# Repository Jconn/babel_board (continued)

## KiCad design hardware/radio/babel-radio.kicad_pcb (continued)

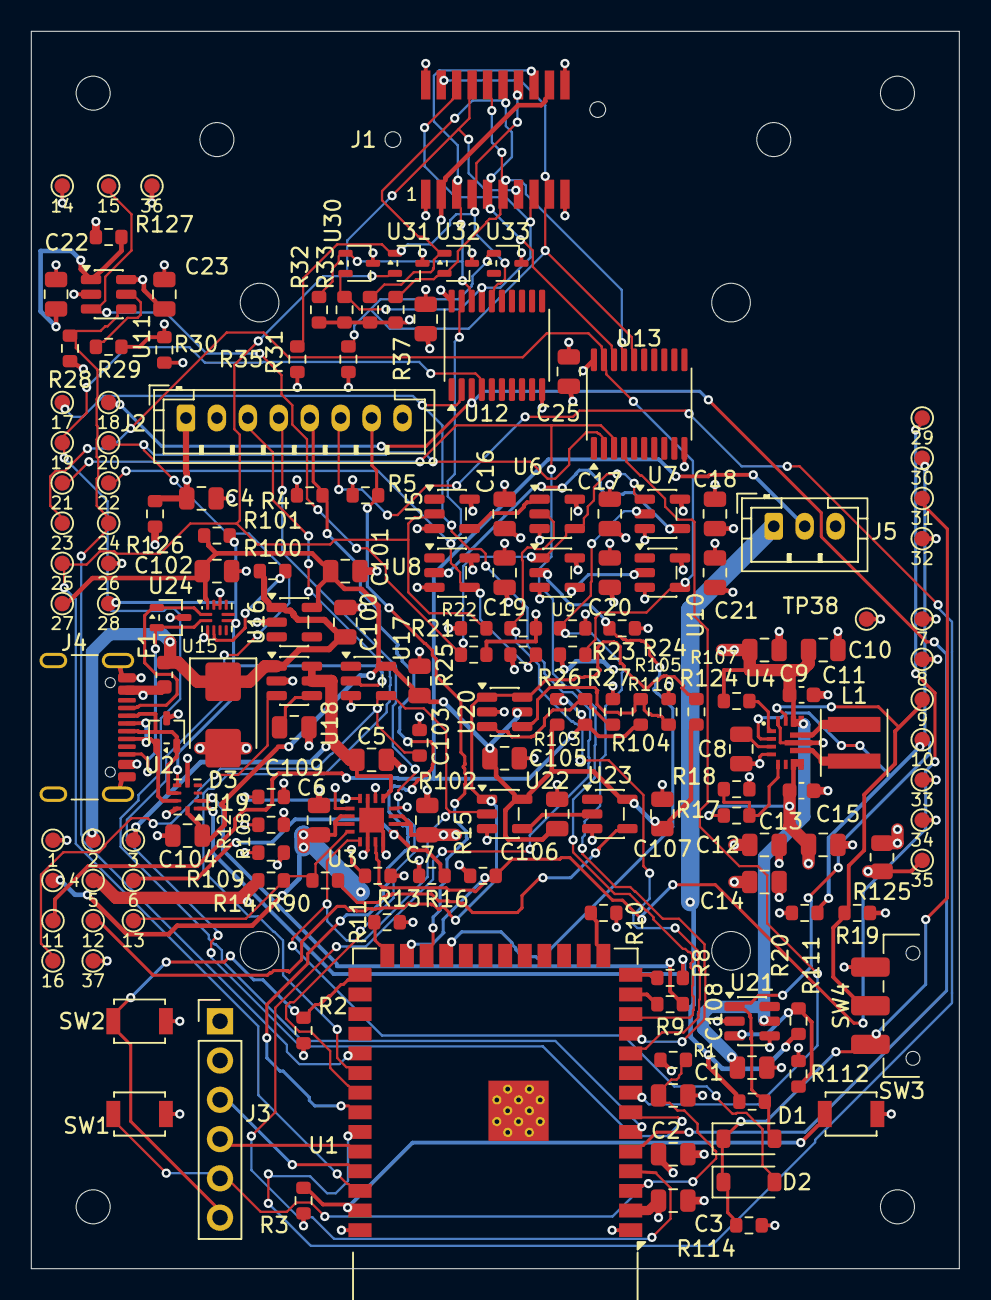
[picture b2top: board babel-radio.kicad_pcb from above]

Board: 4 copper layers, 60.0 x 80.0 mm, 178 parts (0 on the bottom side), 83 nets.

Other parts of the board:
H1, H2, H3, H4, H5, H6, H7, H8, H9, H10: M2 mechanical / NPTH

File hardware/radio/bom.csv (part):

Reference,Value,Assembly,Footprint,Datasheet,Sheet,MPN
U1,ESP32-S3-WROOM-1-N8R8,FIT,RF_Module:ESP32-S3-WROOM-1,https://www.espressif.com/sites/default/files/documentation/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,host,
R1,10k,FIT,Resistor_SMD:R_0603_1608Metric,,host,
C1,1uF / EN delay,FIT,Capacitor_SMD:C_0805_2012Metric,,host,
SW1,B3U-1000P / RESET,FIT,Button_Switch_SMD:SW_SPST_B3U-1000P,,host,
R2,10k,FIT,Resistor_SMD:R_0603_1608Metric,,host,
SW2,B3U-1000P / BOOT,FIT,Button_Switch_SMD:SW_SPST_B3U-1000P,,host,
R3,10k,FIT,Resistor_SMD:R_0603_1608Metric,,host,
SW3,B3U-1000P / USER / HOLD,FIT,Button_Switch_SMD:SW_SPST_B3U-1000P,,host,
C2,22uF / 10V / U1,FIT,Capacitor_SMD:C_0805_2012Metric,,host,
C3,100nF / U1,FIT,Capacitor_SMD:C_0805_2012Metric,,host,
J2,B8B-PH-K-S / OLED cable,FIT,Connector_JST:JST_PH_B8B-PH-K_1x08_P2.00mm_Vertical,https://learn.adafruit.com/adafruit-grayscale-1-5-128x128-ol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,host,
J3,UART RECOVERY / 3.3V ONLY,FIT,Connector_PinHeader_2.54mm:PinHeader_1x06_P2.54mm_Vertical,,host,
R4,10k,FIT,Resistor_SMD:R_0603_1608Metric,,host,
R5,10k,FIT,Resistor_SMD:R_0603_1608Metric,,host,
C4,10uF / display,FIT,Capacitor_SMD:C_0805_2012Metric,,host,
J4,USB4105-GF-A,FIT,Connector_USB:USB_C_Receptacle_GCT_USB4105-xx-A_16P_TopMnt_Horizontal,https://gct.co/files/drawings/usb4105.pdf,usb_charge,
U2,TPD2E2U06DCKR,FIT,Package_TO_SOT_SMD:SOT-323_SC-70,https://www.ti.com/lit/ds/symlink/tpd2e2u06.pdf,usb_charge,
F1,046701.5NR / 1.5A fast fuse,FIT,Fuse:Fuse_0603_1608Metric,,usb_charge,
D3,SMBJ6.0A / VBUS TVS,FIT,Diode_SMD:D_SMB,,usb_charge,SMBJ6.0A-13-F (Diodes Incorporated)
R8,22R / near U1,FIT,Resistor_SMD:R_0603_1608Metric,,usb_charge,
R9,22R / near U1,FIT,Resistor_SMD:R_0603_1608Metric,,usb_charge,
U3,BQ24079RGTR / 4.1V,FIT,Babel:BQ24079_RGT0016B,https://www.ti.com/lit/ds/symlink/bq24074.pdf,usb_charge,
J5,B3B-PH-K-S / Jauch 251555,FIT,Connector_JST:JST_PH_B3B-PH-K_1x03_P2.00mm_Vertical,https://mm.digikey.com/Volume0/opasdata/d220001/medias/docus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,usb_charge,
R10,100k,FIT,Resistor_SMD:R_0603_1608Metric,,usb_charge,
R11,100k,FIT,Resistor_SMD:R_0603_1608Metric,,usb_charge,
R12,5.36k 1% / 166mA,FIT,Resistor_SMD:R_0603_1608Metric,,usb_charge,
R13,1.78k 1% / 904mA,FIT,Resistor_SMD:R_0603_1608Metric,,usb_charge,
R14,10k / disable default,FIT,Resistor_SMD:R_0603_1608Metric,,usb_charge,
R90,0R / enable guard AFTER bench test,DNP,Resistor_SMD:R_0603_1608Metric,,usb_charge,
R15,100k,FIT,Resistor_SMD:R_0603_1608Metric,,usb_charge,
R16,100k,FIT,Resistor_SMD:R_0603_1608Metric,,usb_charge,
C5,1uF / 16V / input,FIT,Capacitor_SMD:C_0805_2012Metric,,usb_charge,
C6,4.7uF / 10V / BAT,FIT,Capacitor_SMD:C_0805_2012Metric,,usb_charge,
C7,4.7uF / 10V / OUT,FIT,Capacitor_SMD:C_0805_2012Metric,,usb_charge,
U4,TPS63070RNMR,FIT,Babel:TPS63070_RNM0015A,https://www.ti.com/lit/ds/symlink/tps63070.pdf,regulator,
R124,10k / PS input protection,FIT,Resistor_SMD:R_0603_1608Metric,,regulator,
L1,1.5uH / XFL4020-152MEC,FIT,Inductor_SMD:L_Coilcraft_XxL4020,https://www.coilcraft.com/pdfs/xfl4020.pdf,regulator,
R17,470k 1%,FIT,Resistor_SMD:R_0603_1608Metric,,regulator,
R18,150k 1%,FIT,Resistor_SMD:R_0603_1608Metric,,regulator,
C8,100nF / VAUX,FIT,Capacitor_SMD:C_0805_2012Metric,,regulator,
C9,10uF / 25V X7S,FIT,Capacitor_SMD:C_0805_2012Metric,,regulator,GRM21BC71E106ME11L
C10,10uF / 25V X7S,FIT,Capacitor_SMD:C_0805_2012Metric,,regulator,GRM21BC71E106ME11L
C11,10uF / 25V close,FIT,Capacitor_SMD:C_0603_1608Metric,,regulator,TMK107BBJ106MA-T
C12,22uF / 16V X6S,FIT,Capacitor_SMD:C_0805_2012Metric,,regulator,GRM21BC81C226ME44L
C13,22uF / 16V X6S,FIT,Capacitor_SMD:C_0805_2012Metric,,regulator,GRM21BC81C226ME44L
C14,22uF / 16V X6S,FIT,Capacitor_SMD:C_0805_2012Metric,,regulator,GRM21BC81C226ME44L
C15,10uF / 25V close,FIT,Capacitor_SMD:C_0603_1608Metric,,regulator,TMK107BBJ106MA-T
SW4,JS102011SAQN / SYSTEM,FIT,Button_Switch_SMD:SW_SPDT_CK_JS102011SAQN,,regulator,
R19,100k,FIT,Resistor_SMD:R_0603_1608Metric,,regulator,
R20,100k,FIT,Resistor_SMD:R_0603_1608Metric,,regulator,
U5,SN74LVC1G04DBVR,FIT,Package_TO_SOT_SMD:SOT-23-5,https://www.ti.com/lit/ds/symlink/sn74lvc1g04.pdf,port_power,
C16,100nF / U5,FIT,Capacitor_SMD:C_0805_2012Metric,,port_power,
U6,SN74LVC1G08DBVR,FIT,Package_TO_SOT_SMD:SOT-23-5,https://www.ti.com/lit/ds/symlink/sn74lvc1g08.pdf,port_power,
C17,100nF / U6,FIT,Capacitor_SMD:C_0805_2012Metric,,port_power,
U7,SN74LVC1G08DBVR,FIT,Package_TO_SOT_SMD:SOT-23-5,https://www.ti.com/lit/ds/symlink/sn74lvc1g08.pdf,port_power,
C18,100nF / U7,FIT,Capacitor_SMD:C_0805_2012Metric,,port_power,
U8,SN74LVC1G04DBVR,FIT,Package_TO_SOT_SMD:SOT-23-5,https://www.ti.com/lit/ds/symlink/sn74lvc1g04.pdf,port_power,
C19,100nF / U8,FIT,Capacitor_SMD:C_0805_2012Metric,,port_power,
U9,SN74LVC1G08DBVR,FIT,Package_TO_SOT_SMD:SOT-23-5,https://www.ti.com/lit/ds/symlink/sn74lvc1g08.pdf,port_power,
C20,100nF / U9,FIT,Capacitor_SMD:C_0805_2012Metric,,port_power,
U10,SN74LVC1G04DBVR,FIT,Package_TO_SOT_SMD:SOT-23-5,https://www.ti.com/lit/ds/symlink/sn74lvc1g04.pdf,port_power,
C21,100nF / U10,FIT,Capacitor_SMD:C_0805_2012Metric,,port_power,
R21,10k,FIT,Resistor_SMD:R_0603_1608Metric,,port_power,
R22,100k,FIT,Resistor_SMD:R_0603_1608Metric,,port_power,
R23,100k,FIT,Resistor_SMD:R_0603_1608Metric,,port_power,
R24,100k,FIT,Resistor_SMD:R_0603_1608Metric,,port_power,
R25,100k,FIT,Resistor_SMD:R_0603_1608Metric,,port_power,
R26,10k,FIT,Resistor_SMD:R_0603_1608Metric,,port_power,
R27,10k,FIT,Resistor_SMD:R_0603_1608Metric,,port_power,
R28,10k,FIT,Resistor_SMD:R_0603_1608Metric,,port_power,
U11,TPS2553DBVR,FIT,Package_TO_SOT_SMD:SOT-23-6,https://www.ti.com/lit/ds/symlink/tps2553.pdf,port_power,
R29,226k 1%,FIT,Resistor_SMD:R_0603_1608Metric,,port_power,
C22,1uF / input,FIT,Capacitor_SMD:C_0805_2012Metric,,port_power,
C23,1uF / output,FIT,Capacitor_SMD:C_0805_2012Metric,,port_power,
R30,10k / discharge,FIT,Resistor_SMD:R_0603_1608Metric,,port_power,
J1,MEC1-110-02-L-D-NP-A,FIT,Babel:MEC1_110_02_NP_A_Socket,https://suddendocs.samtec.com/prints/mec1-1xx-xx-xx-d-xx-xx-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,port_bus,
U12,SN74CB3Q3245PWR,FIT,Package_SO:TSSOP-20_4.4x6.5mm_P0.65mm,https://www.ti.com/lit/ds/symlink/sn74cb3q3245.pdf,port_bus,
C24,100nF / U12,FIT,Capacitor_SMD:C_0805_2012Metric,,port_bus,
U13,SN74CB3Q3245PWR,FIT,Package_SO:TSSOP-20_4.4x6.5mm_P0.65mm,https://www.ti.com/lit/ds/symlink/sn74cb3q3245.pdf,port_bus,
C25,100nF / U13,FIT,Capacitor_SMD:C_0805_2012Metric,,port_bus,
R31,4.7k,FIT,Resistor_SMD:R_0603_1608Metric,,port_bus,
R32,4.7k,FIT,Resistor_SMD:R_0603_1608Metric,,port_bus,
R33,4.7k,FIT,Resistor_SMD:R_0603_1608Metric,,port_bus,
R34,4.7k,FIT,Resistor_SMD:R_0603_1608Metric,,port_bus,
R35,10k,FIT,Resistor_SMD:R_0603_1608Metric,,port_bus,
R37,10k,FIT,Resistor_SMD:R_0603_1608Metric,,port_bus,
U16,TPS70933DBVR,FIT,Package_TO_SOT_SMD:SOT-23-5,https://www.ti.com/lit/ds/symlink/tps709.pdf,usb_policy,
C100,2.2uF / 16V / LDO IN,FIT,Capacitor_SMD:C_0805_2012Metric,,usb_policy,
C101,2.2uF / 10V / LDO OUT,FIT,Capacitor_SMD:C_0805_2012Metric,,usb_policy,
U15,TUSB320LAIRWBR,FIT,Package_DFN_QFN:Texas_X2QFN-12_1.6x1.6mm_P0.4mm,https://www.ti.com/lit/ds/symlink/tusb320lai.pdf,usb_policy,
R100,887k 1%,FIT,Resistor_SMD:R_0603_1608Metric,,usb_policy,
R101,10k,FIT,Resistor_SMD:R_0603_1608Metric,,usb_policy,
C102,100nF / U15,FIT,Capacitor_SMD:C_0805_2012Metric,,usb_policy,
U17,SN74LVC1G04DBVR,FIT,Package_TO_SOT_SMD:SOT-23-5,https://www.ti.com/lit/ds/symlink/sn74lvc1g04.pdf,usb_policy,
C103,100nF / U17,FIT,Capacitor_SMD:C_0805_2012Metric,,usb_policy,
R102,100k,FIT,Resistor_SMD:R_0603_1608Metric,,usb_policy,
U18,TPS22810DBVR,FIT,Package_TO_SOT_SMD:SOT-23-6,https://www.ti.com/lit/ds/symlink/tps22810.pdf,usb_policy,
C109,27nF / slew ~2.2ms at 5V,FIT,Capacitor_SMD:C_0805_2012Metric,,usb_policy,
U19,TS3USB221ARSER,FIT,Package_DFN_QFN:Texas_UQFN-10_1.5x2mm_P0.5mm,https://www.ti.com/lit/ds/symlink/ts3usb221a.pdf,usb_policy,
C104,100nF / U19,FIT,Capacitor_SMD:C_0805_2012Metric,,usb_policy,
U20,TPS3700DDCR,FIT,Package_TO_SOT_SMD:SOT-23-6,https://www.ti.com/lit/ds/symlink/tps3700.pdf,charge_guard,
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
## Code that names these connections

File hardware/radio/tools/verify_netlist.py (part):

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def mapping(ref,pins):
    for number,net in pins.items(): pin(ref,number,net)

mapping('U1',{1:'GND',2:'V3V3',3:'CHIP_EN',40:'GND',41:'GND',
    4:'H_NVM_SCL',5:'H_NVM_SDA',6:'H_NVM_WP',7:'H_SENSOR_IO0',12:'H_SENSOR_IO1',
    8:'H_SENSOR_IO2',
    10:'PWR_REQ',11:'NVM_REQ',23:'SENSOR_REQ',38:'PRESENT_N',31:'PORT_FAULT_N',
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# Reversible insertion: a reversed card puts its contact n on socket contact 21-n.
assert all(port[n-1]==port[20-n] for n in range(1,21))
# Selected Jauch 251555 pack drawing: red / yellow NTC / black.
mapping('J5',{1:'VBAT',2:'PACK_NTC',3:'GND'})
# Babel adapter header, NOT the module's physical pin numbering.
mapping('J2',{1:'V3V3_OLED',2:'GND',3:'LCD_SCK',4:'LCD_MOSI',5:'LCD_CS_N',6:'LCD_DC',7:'LCD_RESET_N'})
assert 'J2.8' in nc
# Compare current daughter export: presence is deliberately grounded there.
daughter=ET.parse(ROOT.parent/'ir-daughter/babel-ir-daughter.net.xml')
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        name={'SENSOR_SCL':'SENSOR_IO0','SENSOR_SDA':'SENSOR_IO1','SENSOR_IRQ_N':'SENSOR_IO2'}.get(net.attrib['name'].lstrip('/'),net.attrib['name'].lstrip('/'))
        assert name==want,(number,want)

mapping('U3',{1:'CHG_TS_FIXED',2:'VBAT',3:'VBAT',4:'CHARGE_DISABLE',5:'USB_ALLOW',6:'GND',
    7:'USB_PGOOD_N',8:'GND',9:'CHG_N',10:'SYS_RAW',11:'SYS_RAW',12:'CHG_ILIM',13:'USB_CHG_IN',14:'CHG_TMR',15:'GND',16:'CHG_ISET',17:'GND'})
mapping('U4',{1:'REG_PS',2:'REG_PG',3:'REG_AUX',4:'GND',5:'REG_FB',7:'V3V3_REG',8:'V3V3_REG',
    9:'REG_L2',10:'GND',11:'REG_L1',12:'SYS_RAW',13:'SYS_RAW',14:'REG_EN',15:'GND'})
mapping('L1',{1:'REG_L1',2:'REG_L2'})
mapping('R124',{1:'SYS_RAW',2:'REG_PS'})
mapping('U11',{1:'V3V3_PORT_IN',2:'GND',3:'PORT_EN',4:'PORT_FAULT_N',5:'PORT_ILIM',6:'VDD_DAUGHTER'})
mapping('U5',{2:'PRESENT_N',4:'PRESENT'})
mapping('U6',{1:'PRESENT',2:'PWR_REQ',4:'PORT_EN'})
mapping('U7',{1:'PORT_EN',2:'NVM_REQ',4:'NVM_ENABLE'})
mapping('U8',{2:'NVM_ENABLE',4:'NVM_OE_N'})
mapping('U9',{1:'PORT_EN',2:'SENSOR_REQ',4:'SENSOR_ENABLE'})
mapping('U10',{2:'SENSOR_ENABLE',4:'SENSOR_OE_N'})
for ref in ['U5','U6','U7','U8','U9','U10']: mapping(ref,{3:'GND',5:'V3V3'})
for ref,oe,names in [('U12','NVM_OE_N',port[4:7]),('U13','SENSOR_OE_N',['SENSOR_IO0','SENSOR_IO1','SENSOR_IO2'])]:
    mapping(ref,{10:'GND',19:oe,20:'V3V3'})
    for i,name in enumerate(names): mapping(ref,{i+2:'H_'+name,18-i:name})
    assert f'{ref}.1' in nc
for ref,net in [('R31','NVM_SCL'),('R32','NVM_SDA'),('R33','SENSOR_IO0'),('R34','SENSOR_IO1'),
                ('R35','NVM_WP'),('R37','SENSOR_IO2')]:
    mapping(ref,{1:'VDD_DAUGHTER',2:net})
assert {f'U13.{n}' for n in [5,6,7,8,9,11,12,13,14,15]} <= nc
mapping('R8',{1:'USB_DP_LINK',2:'USB_DP_MCU'});mapping('R9',{1:'USB_DM_LINK',2:'USB_DM_MCU'})
mapping('U2',{1:'USB_DP',2:'USB_DM',3:'GND'})
mapping('F1',{1:'USB_VBUS_RAW',2:'USB_5V'})
mapping('D3',{1:'USB_5V',2:'GND'})
for num in ['A1','A12','B1','B12','SH']: pin('J4',num,'GND')
for num in ['A4','A9','B4','B9']: pin('J4',num,'USB_VBUS_RAW')
mapping('J4',{'A5':'CC1','B5':'CC2','A6':'USB_DP','B6':'USB_DP','A7':'USB_DM','B7':'USB_DM'})
mapping('U15',{1:'CC1',2:'CC2',3:'GND',4:'CC_VBUS_DET',7:'CC_HIGH_N',10:'GND',11:'GND',12:'V3V3_CC'})
assert {f'U15.{n}' for n in [5,6,8,9]} <= nc
mapping('U16',{1:'USB_5V',2:'GND',5:'V3V3_CC'})
assert {'U16.3','U16.4'} <= nc  # TPS709 EN may float high; NOT another LDO variant.
mapping('U17',{2:'CC_HIGH_N',3:'GND',4:'USB_ALLOW',5:'V3V3_CC'})
mapping('U18',{1:'USB_5V',2:'GND',3:'USB_ALLOW',4:'USB_SLEW',5:'USB_CHG_IN',6:'USB_CHG_IN'})
mapping('C109',{1:'USB_SLEW',2:'GND'})
mapping('U19',{1:'USB_DP_LINK',2:'USB_DM_LINK',5:'GND',6:'CC_HIGH_N',7:'USB_DM',8:'USB_DP',9:'GND',10:'V3V3_CC'})
assert {'U19.3','U19.4'} <= nc
mapping('U21',{1:'BAT_OK',2:'GND',3:'BAT_SENSE',4:'GND',5:'SYS_RAW'})
mapping('U20',{1:'TEMP_OK',2:'GND',3:'TEMP_HOT_SENSE',4:'TEMP_COLD_SENSE',5:'V3V3_CC',6:'TEMP_OK'})
mapping('U22',{1:'TEMP_OK',2:'USB_ALLOW',3:'GND',4:'CHARGE_ALLOWED',5:'V3V3_CC'})
mapping('U23',{2:'CHARGE_ALLOWED',3:'GND',4:'GUARD_DISABLE',5:'V3V3_CC'})
for ref,a,b in [('R14','SYS_RAW','CHARGE_DISABLE'),('R90','CHARGE_DISABLE','GUARD_DISABLE'),
    ('R103','V3V3_CC','PACK_NTC'),('R104','PACK_NTC','TEMP_HOT_SENSE'),
    ('R105','TEMP_HOT_SENSE','GND'),('R106','PACK_NTC','TEMP_COLD_SENSE'),
    ('R107','TEMP_COLD_SENSE','GND'),('R108','CHG_TMR','GND'),
    ('R109','CHG_TS_FIXED','GND'),('R110','V3V3_CC','TEMP_OK')]: mapping(ref,{1:a,2:b})
assert 'U21.6' in nc
for ref, a, b in [('R100','USB_5V','CC_VBUS_DET'),('R101','V3V3_CC','CC_HIGH_N'),
    ('R102','USB_ALLOW','GND'),
    ('R111','VBAT','BAT_SENSE'),('R112','BAT_SENSE','GND'),('R113','VBAT','BAT_OK'),
    ('R114','POWER_AVAILABLE','GND')]: mapping(ref,{1:a,2:b})
mapping('D1',{1:'POWER_AVAILABLE',2:'BAT_OK'});mapping('D2',{1:'POWER_AVAILABLE',2:'USB_ALLOW'})
mapping('SW4',{1:'POWER_AVAILABLE',2:'REG_EN',3:'GND'})
mapping('U24',{1:'CC1',2:'CC2',3:'GND'})
for i,pair in enumerate([('NVM_SCL','NVM_SDA'),('NVM_WP','PRESENT_N'),('SENSOR_IO0','SENSOR_IO1')]):
    mapping(f'U{30+i}',{1:pair[0],2:pair[1],3:'GND'})
mapping('U33',{1:'SENSOR_IO2',3:'GND'}); assert 'U33.2' in nc
parts={c.attrib['ref']:c for c in xml.findall('./components/comp')}
assert 'R6' not in parts and 'R7' not in parts  # No duplicate CC pulldowns.
# Retired with the SPI/UART/RESET contacts; their numbers stay unused.
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                  ('R127','V3V3','V3V3_PORT_IN')]:
    mapping(ref,{1:a,2:b})
    assert parts[ref].findtext('value') == '0R / removable current link'
for ref in ('C12','C13','C14','C15'): mapping(ref,{1:'V3V3_REG',2:'GND'})
mapping('R17',{1:'V3V3_REG',2:'REG_FB'})
mapping('C4',{1:'V3V3_OLED',2:'GND'})
mapping('C22',{1:'V3V3_PORT_IN',2:'GND'})
for i,net in enumerate(['GND','USB_5V','USB_CHG_IN','VBAT','SYS_RAW','CHG_N',
    'GND','V3V3','REG_EN','REG_PG','PACK_NTC','TEMP_OK','CHARGE_DISABLE',
    'VDD_DAUGHTER','PORT_EN','USB_ALLOW','H_NVM_SCL','H_NVM_SDA','H_NVM_WP',
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
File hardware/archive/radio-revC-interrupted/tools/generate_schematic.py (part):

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
p=page('host','PROCESSOR / DISPLAY / RECOVERY',[
    'U1 selected: ESP32-S3-WROOM-1-N8R8. GPIO35/36/37 reserved for octal PSRAM; do not route.',
    'GPIO0 boot; GPIO3/45 strap LOW, reserved. USB current permission is now autonomous hardware, not firmware.',
    'Display: Adafruit 4741 SSD1327 OLED module, 128x128 grayscale. Cut module J1/J2 jumpers for SPI.',
    'J3 is 3.3 V UART recovery; VTREF is sense only. Native USB is on GPIO19/20. Antenna keepout required.'
])
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signals[12]='H_SENSOR_CS_N'
for gpio in (9,10,12,13): signals[gpio]=signals[gpio].replace('H_','MCU_')
add(p,'WROOM','U1','ESP32-S3-WROOM-1-N8R8',
    {1:G,2:V,3:'CHIP_EN',40:G,41:G,**{pin:signals.get(gpio) for pin,gpio in gpio_by_pin.items()}},
    'RF_Module:ESP32-S3-WROOM-1',ESP)
r(p,'10k',V,'CHIP_EN'); c(p,'1uF / EN delay','CHIP_EN'); sw(p,'RESET','CHIP_EN',G)
r(p,'10k',V,'BOOT_N'); sw(p,'BOOT','BOOT_N',G)
r(p,'10k',V,'BUTTON_N'); sw(p,'USER / HOLD','BUTTON_N',G)
c(p,'22uF / 10V / U1',V); c(p,'100nF / U1',V)
add(p,'CONN8','J2','B8B-PH-K-S / OLED cable',{1:V,2:G,3:'LCD_SCK',4:'LCD_MOSI',5:'LCD_CS_N',6:'LCD_DC',7:'LCD_RESET_N',8:None},'Connector_JST:JST_PH_B8B-PH-K_1x08_P2.00mm_Vertical',ds='https://learn.adafruit.com/adafruit-grayscale-1-5-128x128-oled-display/pinouts')
add(p,'CONN6','J3','UART RECOVERY / 3.3V ONLY',{1:G,2:V,3:'DEBUG_TX',4:'DEBUG_RX',5:'CHIP_EN',6:'BOOT_N'},'Connector_PinHeader_2.54mm:PinHeader_1x06_P2.54mm_Vertical')
r(p,'10k',V,'LCD_CS_N'); r(p,'10k',V,'LCD_RESET_N'); c(p,'10uF / display',V)

p=page('usb_charge','USB-C / BATTERY POWER PATH',[
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
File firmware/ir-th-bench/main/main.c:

// Bench bring-up for the IR TH daughter (MLX90614 + 24LC256) through J2.
// GPIOs match the radio (hardware/radio/gpio-map.csv) so the code carries over:
// sensor bus J2.3 SCL -> GPIO7, J2.4 SDA -> GPIO8; NVM bus J2.5 SCL -> GPIO4,
// J2.6 SDA -> GPIO5, J2.7 WP -> GPIO6; J2.2 -> 3V3, J2.1 -> GND.
// Pull-ups are R2-R5 on the daughter; the ESP32's internal ones stay off.

#include <stdio.h>
#include "freertos/FreeRTOS.h"
#include "freertos/task.h"
#include "driver/gpio.h"
#include "driver/i2c_master.h"
#include "esp_log.h"

#define SENSOR_SCL_GPIO 7
#define SENSOR_SDA_GPIO 8
#define NVM_SCL_GPIO    4
#define NVM_SDA_GPIO    5
#define NVM_WP_GPIO     6  // high = write-protected (R1 also pulls it high)
#define BUS_HZ      100000  // MLX90614 is SMBus: 100 kHz max
#define MLX_ADDR    0x5A
#define EEPROM_ADDR 0x50

#define MLX_RAM_TA   0x06  // ambient (die) temperature
#define MLX_RAM_TOBJ 0x07  // object temperature

static const char *TAG = "ir-th-bench";

// SMBus PEC: CRC-8, polynomial x^8 + x^2 + x + 1, initial value 0.
static uint8_t crc8(const uint8_t *d, size_t n)
{
    uint8_t c = 0;
    for (size_t i = 0; i < n; i++) {
        c ^= d[i];
        for (int b = 0; b < 8; b++) {
            c = (c & 0x80) ? (uint8_t)((c << 1) ^ 0x07) : (uint8_t)(c << 1);
        }
    }
    return c;
}

// SMBus "read word": command byte, repeated start, LSB, MSB, PEC.
static esp_err_t mlx_read(i2c_master_dev_handle_t dev, uint8_t cmd, uint16_t *out)
{
    uint8_t rx[3];
    esp_err_t err = i2c_master_transmit_receive(dev, &cmd, 1, rx, sizeof rx, 100);
    if (err != ESP_OK) {
        return err;
    }
    uint8_t frame[5] = { MLX_ADDR << 1, cmd, (MLX_ADDR << 1) | 1, rx[0], rx[1] };
    if (crc8(frame, sizeof frame) != rx[2]) {
        return ESP_ERR_INVALID_CRC;
    }
    *out = rx[0] | (rx[1] << 8);
    return ESP_OK;
}

static void print_temp(const char *name, esp_err_t err, uint16_t raw)
{
    if (err != ESP_OK) {
        printf("%s: %s  ", name, esp_err_to_name(err));
    } else if (raw & 0x8000) {
        printf("%s: sensor error flag (0x%04x)  ", name, raw);
    } else {
        printf("%s: %6.2f C  ", name, raw * 0.02 - 273.15);
    }
}

static i2c_master_bus_handle_t new_bus(int sda, int scl)
{
    i2c_master_bus_config_t cfg = {
        .i2c_port = -1,
        .sda_io_num = sda,
        .scl_io_num = scl,
        .clk_source = I2C_CLK_SRC_DEFAULT,
        .glitch_ignore_cnt = 7,
        .flags.enable_internal_pullup = false,
    };
    i2c_master_bus_handle_t bus;
    ESP_ERROR_CHECK(i2c_new_master_bus(&cfg, &bus));
    return bus;
}

static void scan(i2c_master_bus_handle_t bus, const char *name, uint16_t expect)
{
    printf("%s bus scan:", name);
    int found = 0;
    for (uint16_t a = 0x08; a < 0x78; a++) {
        if (i2c_master_probe(bus, a, 50) == ESP_OK) {
            printf(" 0x%02x", a);
            found++;
        }
    }
    printf("%s (expect 0x%02x)\n", found ? "" : " nothing", expect);
}

// Before the buses start: R2-R5 (4.7k) beat the ESP32's ~45k internal pulls,
// so a powered, wired line reads high with either internal pull.
static void line_check(void)
{
    static const struct { int gpio; const char *name; } lines[] = {
        { SENSOR_SCL_GPIO, "J2.3 sensor SCL" }, { SENSOR_SDA_GPIO, "J2.4 sensor SDA" },
        { NVM_SCL_GPIO, "J2.5 NVM SCL" },       { NVM_SDA_GPIO, "J2.6 NVM SDA" },
        { NVM_WP_GPIO, "J2.7 NVM WP" },
    };
    printf("\nLine check (pulled-down read, pulled-up read):\n");
    for (int i = 0; i < sizeof lines / sizeof lines[0]; i++) {
        int g = lines[i].gpio;
        gpio_reset_pin(g);
        gpio_set_direction(g, GPIO_MODE_INPUT);
        gpio_set_pull_mode(g, GPIO_PULLDOWN_ONLY);
        vTaskDelay(pdMS_TO_TICKS(5));
        int lo = gpio_get_level(g);
        gpio_set_pull_mode(g, GPIO_PULLUP_ONLY);
        vTaskDelay(pdMS_TO_TICKS(5));
        int hi = gpio_get_level(g);
        gpio_set_pull_mode(g, GPIO_FLOATING);
        printf("  GPIO%-2d %-16s %d %d  %s\n", g, lines[i].name, lo, hi,
               lo && hi ? "pulled high (ok)" : !lo && !hi ? "held LOW" : "floating (no pull-up reached)");
    }
}

void app_main(void)
{
    line_check();

    gpio_set_level(NVM_WP_GPIO, 1);
    gpio_set_direction(NVM_WP_GPIO, GPIO_MODE_OUTPUT);

    i2c_master_bus_handle_t sensor_bus = new_bus(SENSOR_SDA_GPIO, SENSOR_SCL_GPIO);
    i2c_master_bus_handle_t nvm_bus = new_bus(NVM_SDA_GPIO, NVM_SCL_GPIO);

    vTaskDelay(pdMS_TO_TICKS(300));  // MLX90614 needs ~250 ms after power-up

    printf("\n");
    scan(sensor_bus, "sensor", MLX_ADDR);
    scan(nvm_bus, "NVM", EEPROM_ADDR);
    printf("\n");

    i2c_device_config_t mlx_cfg = {
        .dev_addr_length = I2C_ADDR_BIT_LEN_7,
        .device_address = MLX_ADDR,
        .scl_speed_hz = BUS_HZ,
    };
    i2c_device_config_t eeprom_cfg = mlx_cfg;
    eeprom_cfg.device_address = EEPROM_ADDR;
    i2c_master_dev_handle_t mlx, eeprom;
    ESP_ERROR_CHECK(i2c_master_bus_add_device(sensor_bus, &mlx_cfg, &mlx));
    ESP_ERROR_CHECK(i2c_master_bus_add_device(nvm_bus, &eeprom_cfg, &eeprom));

    // Read-only EEPROM check: a blank 24LC256 reads 0xff.
    uint8_t addr[2] = { 0x00, 0x00 };
    uint8_t data[16];
    esp_err_t err = i2c_master_transmit_receive(eeprom, addr, sizeof addr, data, sizeof data, 100);
    if (err == ESP_OK) {
        printf("EEPROM 0x0000:");
        for (int i = 0; i < sizeof data; i++) {
            printf(" %02x", data[i]);
        }
        printf("\n\n");
    } else {
        ESP_LOGE(TAG, "EEPROM read failed: %s", esp_err_to_name(err));
    }

    while (1) {
        uint16_t ta = 0, to = 0;
        esp_err_t ea = mlx_read(mlx, MLX_RAM_TA, &ta);
        esp_err_t eo = mlx_read(mlx, MLX_RAM_TOBJ, &to);
        print_temp("ambient", ea, ta);
        print_temp("object", eo, to);
        printf("\n");
        vTaskDelay(pdMS_TO_TICKS(500));
    }
}

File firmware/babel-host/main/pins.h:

// Host pins, matching the radio (hardware/radio/gpio-map.csv) and the J2 bench wiring.
#pragma once

#define PIN_SENSOR_SCL 7  // J2.3, radio H_SENSOR_IO0
#define PIN_SENSOR_SDA 8  // J2.4, radio H_SENSOR_IO1
#define PIN_NVM_SCL    4  // J2.5
#define PIN_NVM_SDA    5  // J2.6
#define PIN_NVM_WP     6  // J2.7, high = write-protected
